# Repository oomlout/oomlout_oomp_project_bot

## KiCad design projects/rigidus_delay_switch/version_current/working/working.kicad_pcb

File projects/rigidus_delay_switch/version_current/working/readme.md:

# OOMP Project  
## delay_switch  by rigidus  
  
oomp key: oomp_projects_flat_rigidus_delay_switch  
(snippet of original readme)  
  
- delay_switch  
  
  full source readme at [readme_src.md](readme_src.md)  
  
source repo at: [https://github.com/rigidus/delay_switch](https://github.com/rigidus/delay_switch)  
## Board  

## Schematic  

[schematic pdf](working_schematic.pdf)  
## Images

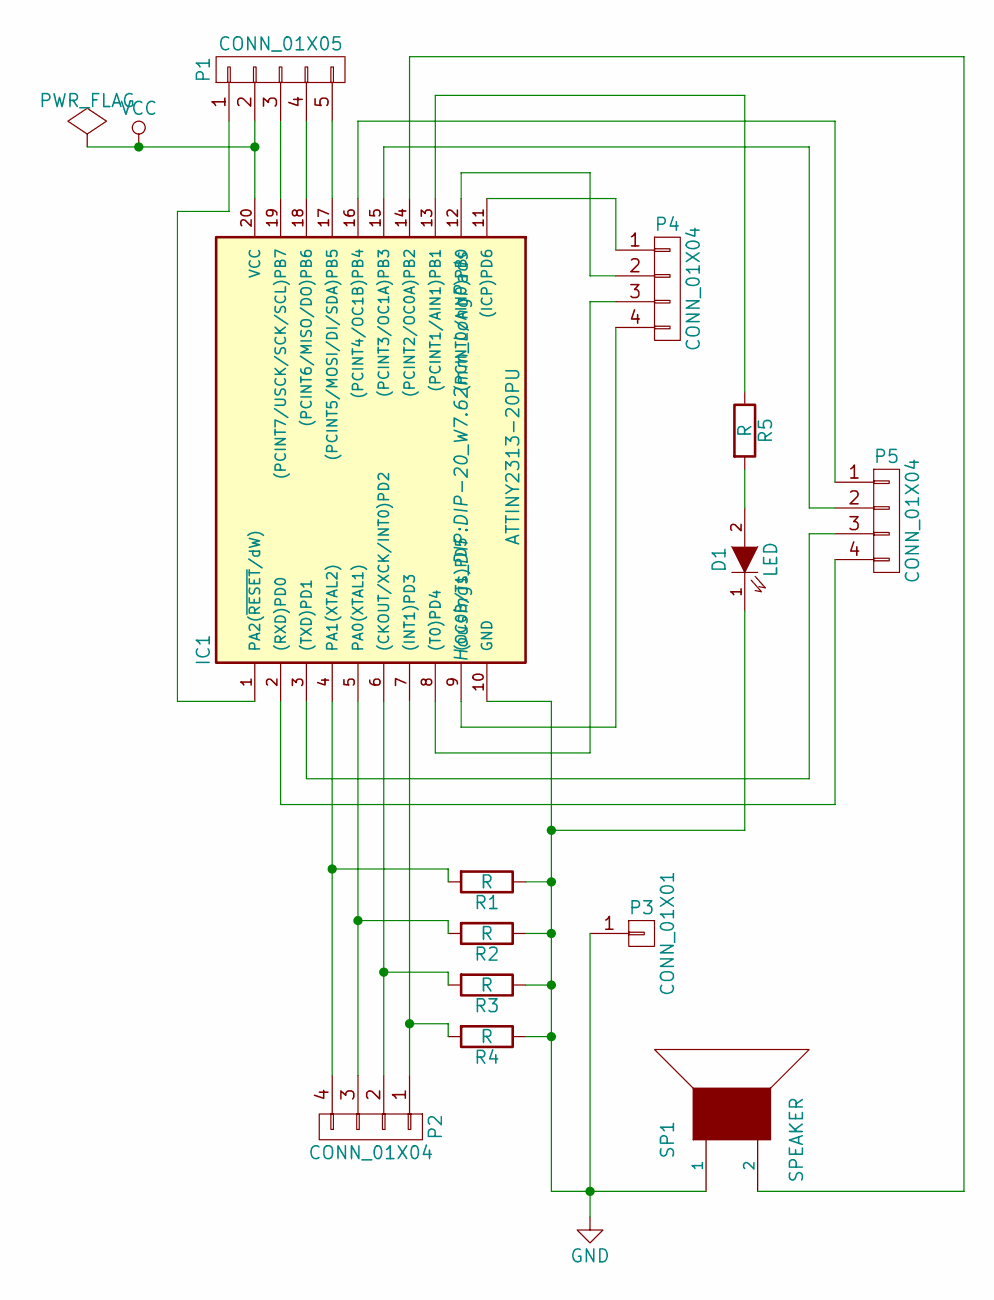
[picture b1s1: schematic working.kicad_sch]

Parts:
D1: LED; LED-3MM
IC1: ATTINY2313-20PU; DIP-20_W7.62mm_LongPads
P1: CONN_01X05; Pin_Header_Straight_1x05
P2, P4, P5: CONN_01X04; Pin_Header_Straight_1x04
P3: CONN_01X01; Pin_Header_Angled_1x01
R1, R2, R3, R4, R5: R; R_1206
SP1: SPEAKER; WireConnection_0.80mmDrill

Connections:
GND: D1.1 (K), IC1.10 (GND), P3.1, R1.1, R2.1, R3.1, R4.1, SP1.1
unnamed: D1.2 (A), R5.2
unnamed: IC1.1 (PA2(~RESET/dW)), P1.1
unnamed: IC1.2 ((RXD)PD0), P5.4
unnamed: IC1.3 ((TXD)PD1), P5.3
unnamed: IC1.4 (PA1(XTAL2)), P2.4, R1.2
unnamed: IC1.5 (PA0(XTAL1)), P2.3, R2.2
unnamed: IC1.6 ((CKOUT/XCK/INT0)PD2), P2.2, R3.2
unnamed: IC1.7 ((INT1)PD3), P2.1, R4.2
unnamed: IC1.8 ((T0)PD4), P4.3
unnamed: IC1.9 ((OC0B/T1)PD5), P4.4
unnamed: IC1.11 ((ICP)PD6), P4.1
unnamed: IC1.12 ((PCINT0/AIN0)PB0), P4.2
unnamed: IC1.13 ((PCINT1/AIN1)PB1), R5.1
unnamed: IC1.14 ((PCINT2/OC0A)PB2), SP1.2
unnamed: IC1.15 ((PCINT3/OC1A)PB3), P5.2
unnamed: IC1.16 ((PCINT4/OC1B)PB4), P5.1
unnamed: IC1.17 ((PCINT5/MOSI/DI/SDA)PB5), P1.5
unnamed: IC1.18 ((PCINT6/MISO/DO)PB6), P1.4
unnamed: IC1.19 ((PCINT7/USCK/SCK/SCL)PB7), P1.3
VCC: IC1.20 (VCC), P1.2

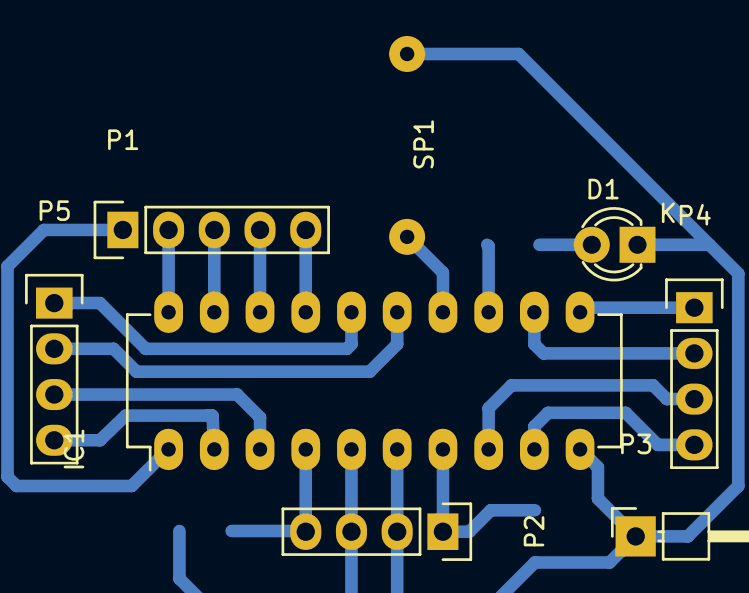
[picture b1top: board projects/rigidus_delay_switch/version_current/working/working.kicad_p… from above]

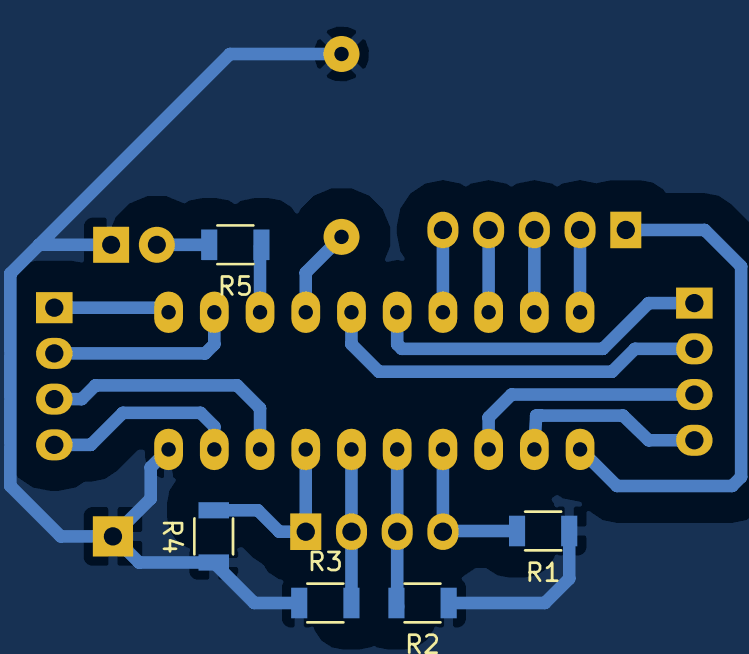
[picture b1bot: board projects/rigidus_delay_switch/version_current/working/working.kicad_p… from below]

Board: 2 copper layers, 13 parts (5 on the bottom side), 21 nets.

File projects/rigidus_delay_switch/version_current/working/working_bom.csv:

"Id";"Designator";"Footprint";"Quantity";"Designation";"Supplier and ref";
1;"D1";"LED-3MM";1;"LED";;;
2;"IC1";"DIP-20_W7.62mm_LongPads";1;"ATTINY2313-20PU";;;
3;"P1";"Pin_Header_Straight_1x05";1;"CONN_01X05";;;
4;"P2,P4,P5";"Pin_Header_Straight_1x04";3;"CONN_01X04";;;
5;"P3";"Pin_Header_Angled_1x01";1;"CONN_01X01";;;
6;"R1,R2,R3,R4,R5";"R_1206";5;"R";;;
7;"SP1";"WireConnection_0.80mmDrill";1;"SPEAKER";;;

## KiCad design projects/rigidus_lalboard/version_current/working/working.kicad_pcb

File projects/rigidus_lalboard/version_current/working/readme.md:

# lalboard by rigidus  
This is a harvested standardized copy of a project from github.  
The original project can be found at:  
https://github.com/rigidus/lalboard  
Please consult that link for additional, details, files, and license information.  
Note: It was auto harvested and if the original repo had more than one board file or anything out of the ordinary the files here are likely not representative.

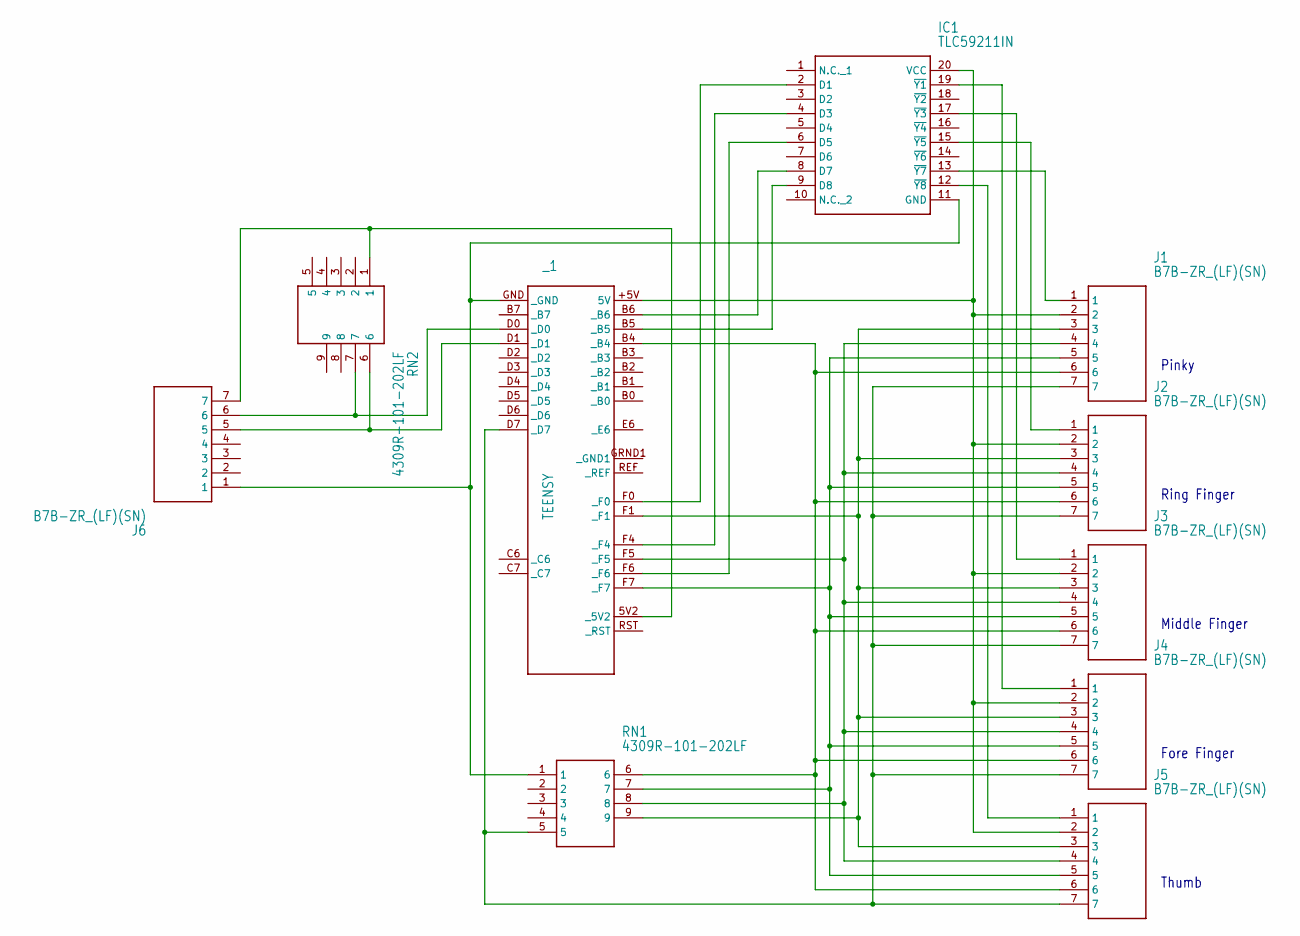
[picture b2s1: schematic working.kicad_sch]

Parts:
IC1: TLC59211IN; DIP794W53P254L2540H508Q20N
J1, J2, J3, J4, J5, J6: B7B-ZR_(LF)(SN); SHDR7W50P0X150_1X7_1200X350X45
RN1, RN2: 4309R-101-202LF; 4309R-101
_1: TEENSY

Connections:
unnamed: IC1.20 (VCC), J1.2, J2.2, J3.2, J4.2, J5.2, _1.+5V (5V)
unnamed: J1.3, J2.3, J3.3, J4.3, J5.3, RN1.9, _1.F1 (_F1)
unnamed: J1.6, J2.6, J3.6, J4.6, J5.6, RN1.6, _1.B4 (_B4)
unnamed: J1.4, J2.4, J3.4, J4.4, J5.4, RN1.8, _1.F5 (_F5)
unnamed: J1.5, J2.5, J3.5, J4.5, J5.5, RN1.7, _1.F7 (_F7)
unnamed: IC1.11 (GND), J6.1, RN1.1, _1.GND (_GND)
unnamed: J1.7, J2.7, J3.7, J4.7, J5.7, RN1.5, _1.D7 (_D7)
unnamed: IC1.8 (D7), _1.B6 (_B6)
unnamed: IC1.9 (D8), _1.B5 (_B5)
unnamed: IC1.6 (D5), _1.F6 (_F6)
unnamed: IC1.4 (D3), _1.F4 (_F4)
unnamed: IC1.2 (D1), _1.F0 (_F0)
unnamed: IC1.15 (~Y5), J2.1
unnamed: J6.5, RN2.6, _1.D1 (_D1)
unnamed: J6.7, RN2.1, _1.5V2 (_5V2)
unnamed: J6.6, RN2.7, _1.D0 (_D0)
unnamed: IC1.17 (~Y3), J3.1
unnamed: IC1.19 (~Y1), J4.1
unnamed: IC1.12 (~Y8), J5.1
unnamed: IC1.13 (~Y7), J1.1

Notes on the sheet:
Thumb
Middle Finger
Fore Finger
Ring Finger
Pinky

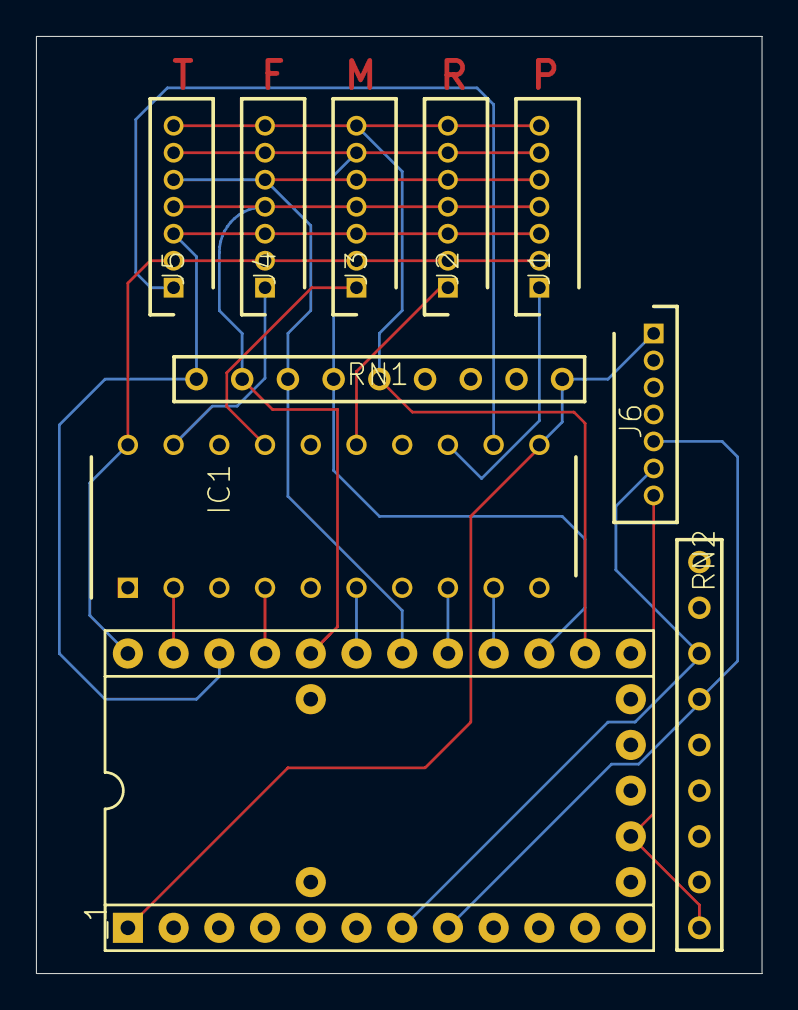
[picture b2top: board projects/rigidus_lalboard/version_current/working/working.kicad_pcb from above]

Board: 2 copper layers, 40.3 x 52.1 mm, 10 parts (0 on the bottom side), 20 nets.

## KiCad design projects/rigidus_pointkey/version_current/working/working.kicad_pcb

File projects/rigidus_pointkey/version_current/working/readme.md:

# pointkey by rigidus  
This is a harvested standardized copy of a project from github.  
The original project can be found at:  
https://github.com/rigidus/pointkey  
Please consult that link for additional, details, files, and license information.  
Note: It was auto harvested and if the original repo had more than one board file or anything out of the ordinary the files here are likely not representative.

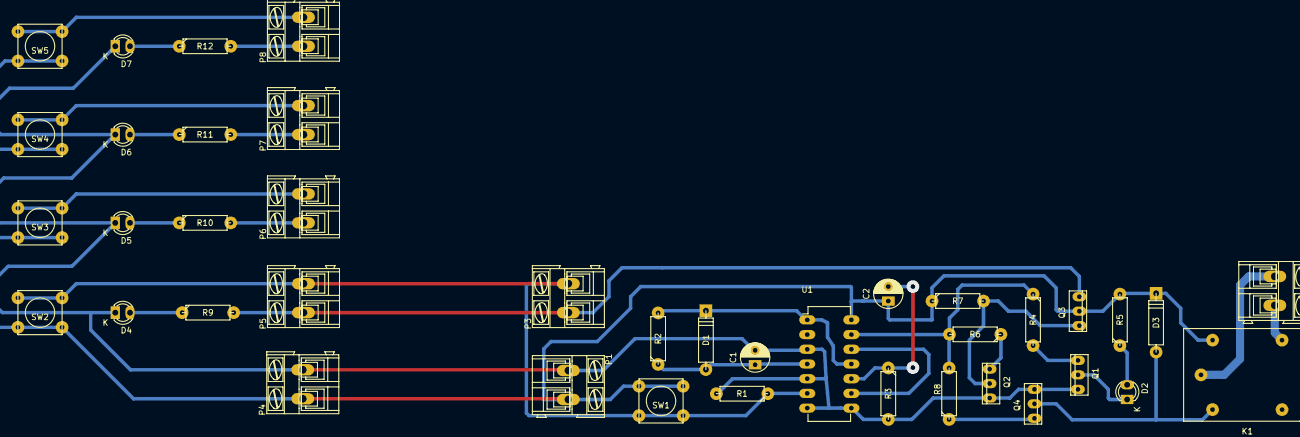
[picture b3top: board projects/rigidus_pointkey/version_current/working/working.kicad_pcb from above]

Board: 2 copper layers, 40 parts (0 on the bottom side), 28 nets.

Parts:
C1: 1u; C_Radial_D5_L6_P2.5
C2: 20u; C_Radial_D5_L6_P2.5
D1, D3: D; D4
D2, D4, D5, D6, D7: LED; LED-3MM
K1: RELAY_1RT; RELAY_812H_1C_C
P1, P2, P3, P4, P5, P6, P7, P8: CONN_01X02; AK300-2
Q1, Q2, Q3, Q4: КТ315; кт-13
R1, R3: 22k; R3-5
R2: 510k; R3-5
R4, R5, R6: 100; R3-5
R7: 1K; R3-5
R8: 1k; R3-5
R9, R10, R11, R12: R; R3-5
SW1, SW2, SW3, SW4, SW5: SW_PUSH; SW_PUSH_SMALL
U1: 4013; DIP-14_W7.62mm

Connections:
GND: C1.2, D4.1, D5.1, D6.1, D7.1, P1.1, P4.2, Q1.3, Q2.3, Q4.3, R1.2, R3.2, U1.3, U1.5, U1.7, U1.8
IND_1: P3.1, P5.1, Q3.3, R9.2
IND_2: P6.1, R10.2
IND_3: P7.1, R11.2
IND_4: P8.1, R12.2
unnamed: C1.1, D1.2, R2.1, U1.4
unnamed: C2.2, R3.1, U1.10
unnamed: D1.1, R2.2, U1.1, U1.11
unnamed: D2.1, Q1.1
unnamed: D2.2, R5.1
unnamed: D3.2, K1.2, Q4.1
unnamed: D4.2, R9.1
unnamed: D5.2, R10.1
unnamed: D6.2, R11.1
unnamed: D7.2, R12.1
unnamed: K1.3, P2.1
unnamed: K1.5, P2.2
unnamed: Q1.2, R4.2
unnamed: Q2.1, Q3.2, R7.2
unnamed: Q2.2, R6.1
unnamed: Q4.2, R8.1
unnamed: R4.1, R6.2, R8.2, U1.13
unnamed: U1.9, U1.12
SWI_1: P3.2, P5.2, R1.1, SW1.1, SW2.2, U1.6
SWI_2: P6.2, SW3.2
SWI_3: P7.2, SW4.2
SWI_4: P8.2, SW5.2
VCC: C2.1, D3.1, K1.1, P1.2, P4.1, Q3.1, R5.2, R7.1, SW1.2, SW2.1, SW3.1, SW4.1, SW5.1, U1.14

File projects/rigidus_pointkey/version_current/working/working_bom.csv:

"Id";"Designator";"Footprint";"Quantity";"Designation";"Supplier and ref";
1;"SW2,SW1,SW3,SW4,SW5";"SW_PUSH_SMALL";5;"SW_PUSH";;;
2;"R3,R1";"R3-5";2;"22k";;;
3;"C1";"C_Radial_D5_L6_P2.5";1;"1u";;;
4;"C2";"C_Radial_D5_L6_P2.5";1;"20u";;;
5;"D1,D3";"D4";2;"D";;;
6;"D2,D4,D5,D6,D7";"LED-3MM";5;"LED";;;
7;"K1";"RELAY_812H_1C_C";1;"RELAY_1RT";;;
8;"Q1,Q2,Q3,Q4";"кт-13";4;"КТ315";;;
9;"R2";"R3-5";1;"510k";;;
10;"R4,R5,R6";"R3-5";3;"100";;;
11;"R7";"R3-5";1;"1K";;;
12;"R8";"R3-5";1;"1k";;;
13;"U1";"DIP-14_W7.62mm";1;"4013";;;
14;"R9,R10,R11,R12";"R3-5";4;"R";;;

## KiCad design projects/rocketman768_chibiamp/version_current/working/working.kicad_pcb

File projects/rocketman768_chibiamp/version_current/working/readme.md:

# ChibiAmp by rocketman768  
This is a harvested standardized copy of a project from github.  
The original project can be found at:  
https://github.com/rocketman768/ChibiAmp  
Please consult that link for additional, details, files, and license information.  
Note: It was auto harvested and if the original repo had more than one board file or anything out of the ordinary the files here are likely not representative.

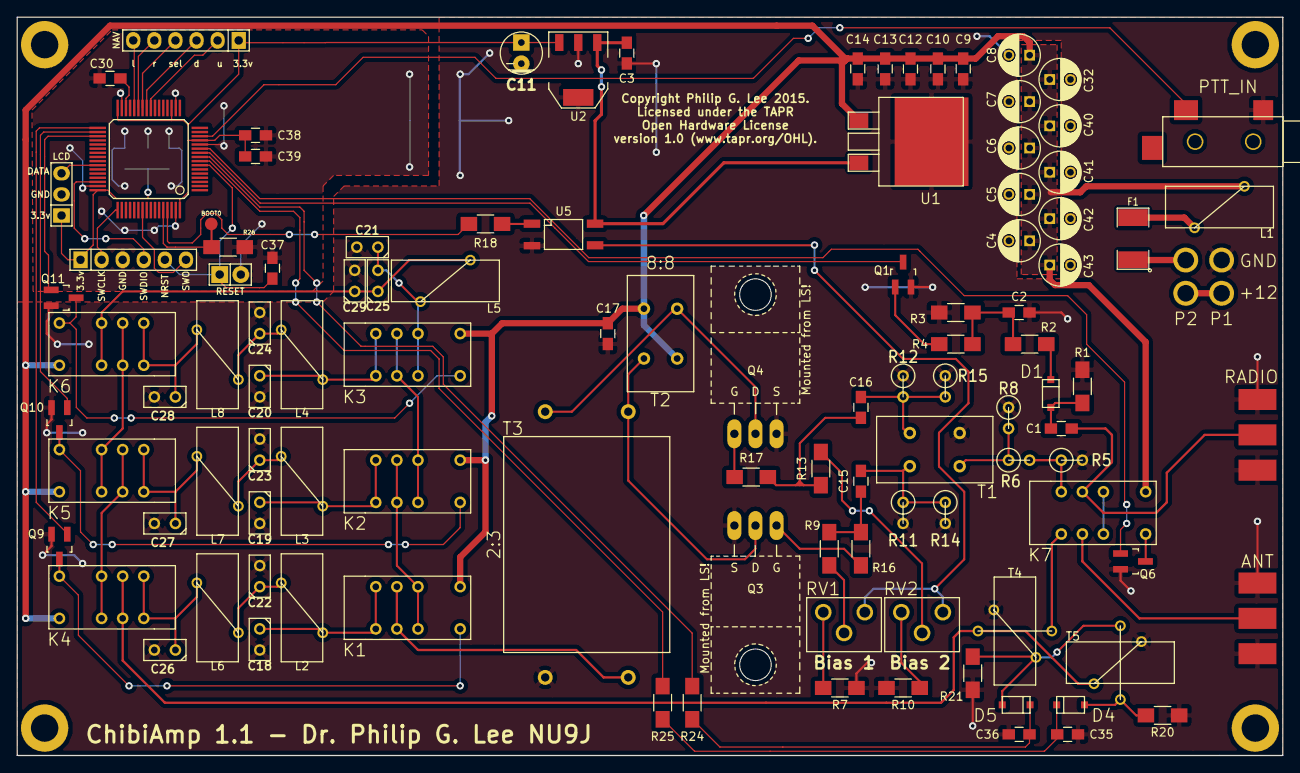
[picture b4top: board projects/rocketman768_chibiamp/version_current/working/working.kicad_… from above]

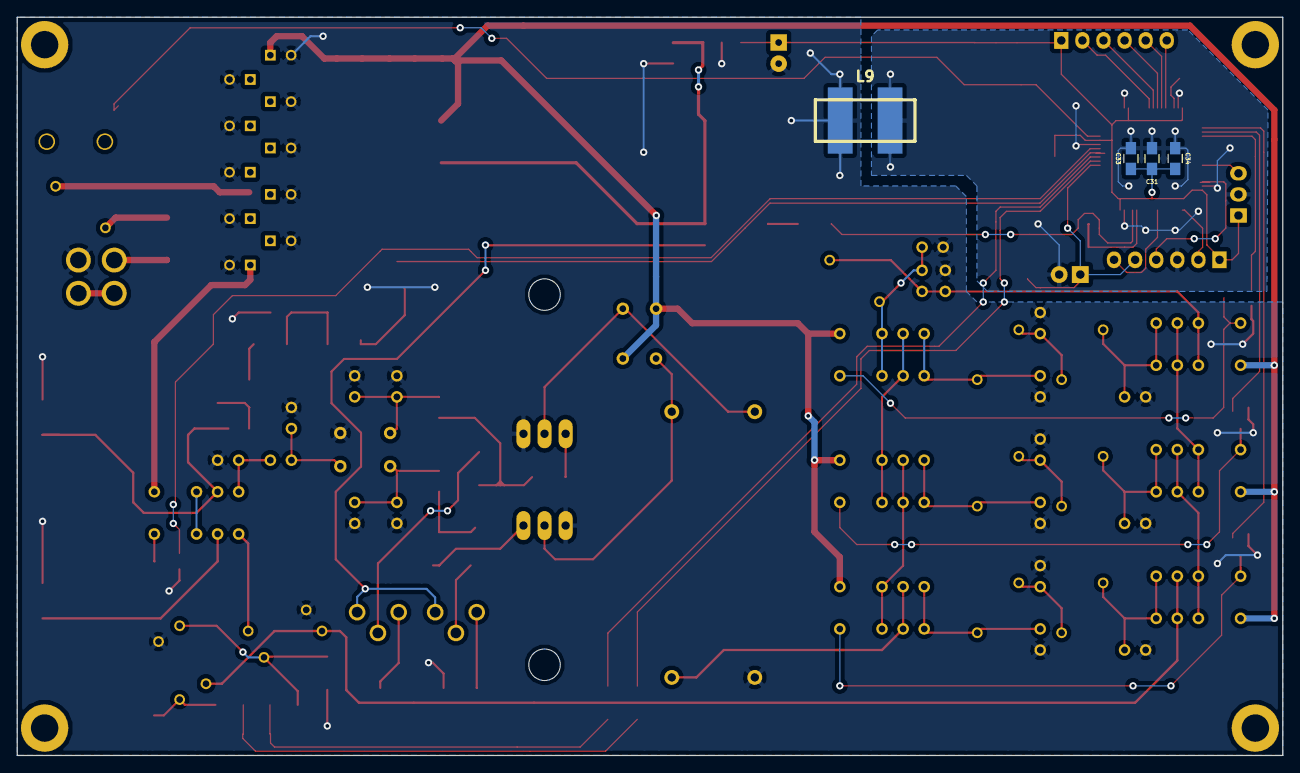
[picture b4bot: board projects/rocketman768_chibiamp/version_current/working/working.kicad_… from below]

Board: 2 copper layers, 152.4 x 88.9 mm, 118 parts (4 on the bottom side), 78 nets.

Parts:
C1, C2, C3, C9, C10, C12, C13, C14, C33, C34, C37: .1u; C_0805_HandSoldering
C4, C5, C6, C7, C8, C32, C40, C41, C42, C43: 10u; C_Radial_D5_L11_P2.5
C11: 10u; Capacitor5x11RM2.5
C15, C16, C17, C35, C36: 0.1u; C_0805_HandSoldering
C18, C25, C26: 150p; C1
C19, C27: 330p; C1
C20, C28: 560p; C1
C21, C29: 1800p; C1
C22: 270p; C1
C23: 680p; C1
C24: 1000p; C1
C30, C31: 4.7u; C_0805_HandSoldering
C38: .01u; C_0805_HandSoldering
C39: 1u; C_0805_HandSoldering
D1, D4, D5: SD101; SOD-123
F1: PTS18128V200; SMD-1812_l
K1: BAND3_IN; EC2-12NU
K2: BAND2_IN; EC2-12NU
K3: BAND1_IN; EC2-12NU
K4: BAND3_OUT; EC2-12NU
K5: BAND2_OUT; EC2-12NU
K6: BAND1_OUT; EC2-12NU
K7: ANT_RLY; EC2-12NU
L1: 500u; TOROID-50
L2, L6: T50-6 8T; TOROID-50
L3, L7: T50-6 9T; TOROID-50
L4, L8: T50-2 12T; TOROID-50
L5: T50-2 17T; TOROID-50
L9: BEAD; WE-SUCKW
Mounting Hole: VAL**; MountingHole4-40
Mounting Hole#2, Mounting Hole#3, Mounting Hole#4: VAL**; MountingHole4-40
P1: PWR; PWR2-16AWG
P2: PWR_SW; PWR2-16AWG
P3: SWD; Pin_Header_Straight_1x06
P4: ANT; SMA-EDGE-0.375in
P5: RADIO; SMA-EDGE-0.375in
P6: PTT_IN; 3.5MM_SWITCHCRAFT-35RASMT2AHNTRX
P7: TP; Measurement_Point_Round-SMD-Pad_Small
P8: NAV_BUTTON; Pin_Header_Straight_1x06
Q1: MMBT6427; SOT-23-EBC_HandSoldering
Q3, Q4: IRF510; TO-220_FET-GDS_Horizontal_MountedFromLS_LargePads
Q6, Q9, Q10, Q11: MMBF170; SOT-23-DGS_HandSoldering
R1, R4, R9, R13, R26: 10k; R_1206_HandSoldering
R2: 680; R_1206_HandSoldering
R3: 6.8k; R_1206_HandSoldering
R5, R8: 300; R1
R6: 18; R1
R7, R10: 5k; R_1206_HandSoldering
R11, R12, R14, R15: 51; R1
R16, R17: 10; R_1206_HandSoldering
R18: 150; R_1206_HandSoldering
R20, R21: 51; R_1206_HandSoldering
R24, R25: 50k; R_1206_HandSoldering
RV1, RV2: 5k; Potentiometer_Trimmer_Piher_PT10_H01
SW1: SW_PUSH; Pin_Header_Straight_1x02
T1, T2: 8:8; BN2-202
T3: 2:3; BN2-3312
T4: 12:1; TOROID2-50-singleturn
T5: 1:12; TOROID2-50-singleturn
U1: LM7805; DPAK-3_VIVOGND
U2: LM3940; SOT-223
U3: LCD-2x16; Pin_Header_Straight_1x03
U4: STM32F401xB/C-LQFP; LQFP64
U5: LTV-356T; Optocoupler_SMD_HandSoldering_KPC357_LTV35x_PC357_SingleCha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

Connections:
+3.3V: C11.1, C31.1, C33.1, C34.1, C38.1, C39.1, P3.1, P8.1, U2.VO, U3.1, U4.13, U4.19, U4.32, U4.48, U4.64
+5V: C3.1, U1.VO, U2.VI, U5.4
+12V: C4.1, C5.1, C6.1, C7.1, C8.1, C9.1, C10.1, C12.1, C13.1, C14.1, C17.2, C32.1, C40.1, C41.1, C42.1, C43.1, K1.1, K2.1, K3.1, K4.1, K5.1, K6.1, K7.1, L1.2, T2.1, T2.4, U1.VI
/Amplifier/amp_in: K7.5, R5.1, R6.2
/Amplifier/amp_on: R18.2, U4.61
/Amplifier/amp_out: K1.4, K1.9, T3.3
/Amplifier/vb1: C15.1, R9.1, R16.2
/Amplifier/vb2: C16.1, R13.1, R17.2
/Band Filters/band1_sel: K3.12, K6.12, Q11.D
/Band Filters/band2_sel: K2.12, K5.12, Q10.D
/Band Filters/band3_sel: K1.12, K4.12, Q9.D
/Band Filters/bandfilter_1sel: Q11.G, U4.35
/Band Filters/bandfilter_2sel: Q10.G, U4.34
/Band Filters/bandfilter_3sel: Q9.G, U4.33
/Band Filters/bandfilter_out: K4.4, K4.9, T4.1, T5.4
/Microcontroller/NRST: C37.1, P3.5, SW1.1, U4.7
/Microcontroller/SWCLK: P3.2, U4.49
/Microcontroller/SWDIO: P3.4, U4.46
/Microcontroller/SWO: P3.6, U4.55
/Microcontroller/mcu_ptt: P6.2, U4.14
/Microcontroller/mcu_rfdet: Q1.c, U4.10
/Microcontroller/mcu_swr_fwd: C36.1, D5.2, R25.1
/Microcontroller/mcu_swr_ref: C35.1, D4.2, R24.2
/Microcontroller/nav_down: P8.3, U4.25
/Microcontroller/nav_left: P8.6, U4.28
/Microcontroller/nav_right: P8.5, U4.27
/Microcontroller/nav_select: P8.4, U4.26
/Microcontroller/nav_up: P8.2, U4.24
/RF In/Out/ant_sw_rly: Q6.G, U4.11
/RF In/Out/from_final: K7.8, T4.2
/RF In/Out/raw_input: C1.2, K7.4, P5.1
DGND: C30.1, C31.2, C33.2, C34.2, C37.2, C38.2, C39.2, L9.2, P3.3, R26.1, SW1.2, U3.2, U4.12, U4.18, U4.31, U4.47, U4.63
GND: C2.1, C3.2, C4.2, C5.2, C6.2, C7.2, C8.2, C9.2, C10.2, C11.2, C12.2, C13.2, C14.2, C17.1, C18.2, C19.2, C20.2, C21.2, C22.2, C23.2, C24.2, C26.2, C27.2, C28.2, C29.2, C32.2, C35.2, C36.2, C40.2, C41.2, C42.2, C43.2, L9.1, P1.1, P4.2, P5.2, P6.1, Q1.e, Q3.S, Q4.S, Q6.S, Q9.S, Q10.S, Q11.S, R1.2, R3.1, R5.2, R7.2, R8.1, R10.2, R11.2, R12.1, R14.2, R15.1, R20.2, R21.2, T1.1, T3.4, T4.3, T5.3, U1.GND, U2.GND, U5.2
unnamed: C1.1, D1.1, R1.1
unnamed: C2.2, R2.1, R3.2, R4.2
unnamed: C15.2, R11.1, R14.1, T1.4
unnamed: C16.2, R12.2, R15.2, T1.2
unnamed: C18.1, K1.5, K1.8, L2.1
unnamed: C19.1, K2.5, K2.8, L3.1
unnamed: C20.1, K3.5, K3.8, L4.1
unnamed: C21.1, C25.2, K3.3, K3.10, L5.1
unnamed: C22.1, L2.2, L6.1
unnamed: C23.1, L3.2, L7.1
unnamed: C24.1, L4.2, L8.1
unnamed: C25.1, C29.1, K6.3, K6.10, L5.2
unnamed: C26.1, K4.5, K4.8, L6.2
unnamed: C27.1, K5.5, K5.8, L7.2
unnamed: C28.1, K6.5, K6.8, L8.2
unnamed: C30.2, U4.30
unnamed: D1.2, R2.2
unnamed: D4.1, R20.1, T5.2
unnamed: D5.1, R21.1, T4.4, T5.1
unnamed: F1.1, P2.2
unnamed: F1.2, L1.1
unnamed: K1.3, K1.10, K2.4, K2.9
unnamed: K2.3, K2.10, K3.4, K3.9
unnamed: K4.3, K4.10, K5.4, K5.9
unnamed: K5.3, K5.10, K6.4, K6.9
unnamed: K7.9, P4.1
unnamed: K7.3, K7.10
unnamed: K7.12, Q6.D
unnamed: P1.2, P2.1
unnamed: P7.1, R26.2, U4.60
unnamed: Q1.b, R4.1
unnamed: Q3.D, T2.3, T3.1
unnamed: Q3.G, R16.1
unnamed: Q4.D, T2.2, T3.2
unnamed: Q4.G, R17.1
unnamed: R6.1, R8.2, T1.3
unnamed: R7.1, RV1.3
unnamed: R9.2, RV1.2
unnamed: R10.1, RV2.3
unnamed: R13.2, RV2.2
unnamed: R18.1, U5.1
unnamed: R24.1, U4.8
unnamed: R25.2, U4.9
unnamed: RV1.1, RV2.1, U5.3
unnamed: U3.3, U4.42

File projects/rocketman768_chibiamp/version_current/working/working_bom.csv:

"Id";"Designator";"Footprint";"Quantity";"Designation";"Supplier and ref";
1;"U2";"SOT-223";1;"LM3940";;;
2;"RV2,RV1";"Potentiometer_Trimmer_Piher_PT10_H01";2;"5k";;;
3;"Q3,Q4";"TO-220_FET-GDS_Horizontal_MountedFromLS_LargePads";2;"IRF510";;;
4;"P1";"PWR2-16AWG";1;"PWR";;;
5;"U5";"Optocoupler_SMD_HandSoldering_KPC357_LTV35x_PC357_SingleChannel";1;"LTV-356T";;;
6;"L9";"WE-SUCKW";1;"BEAD";;;
7;"U4";"LQFP64";1;"STM32F401xB/C-LQFP";;;
8;"L1";"TOROID-50";1;"500u";;;
9;"K7";"EC2-12NU";1;"ANT_RLY";;;
10;"K5";"EC2-12NU";1;"BAND2_OUT";;;
11;"K4";"EC2-12NU";1;"BAND3_OUT";;;
12;"K1";"EC2-12NU";1;"BAND3_IN";;;
13;"K2";"EC2-12NU";1;"BAND2_IN";;;
14;"K3";"EC2-12NU";1;"BAND1_IN";;;
15;"K6";"EC2-12NU";1;"BAND1_OUT";;;
16;"P4";"SMA-EDGE-0.375in";1;"ANT";;;
17;"P5";"SMA-EDGE-0.375in";1;"RADIO";;;
18;"D1,D4,D5";"SOD-123";3;"SD101";;;
19;"T4";"TOROID2-50-singleturn";1;"12:1";;;
20;"T5";"TOROID2-50-singleturn";1;"1:12";;;
21;"L4,L8";"TOROID-50";2;"T50-2 12T";;;
22;"L3,L7";"TOROID-50";2;"T50-6 9T";;;
23;"L5";"TOROID-50";1;"T50-2 17T";;;
24;"L6,L2";"TOROID-50";2;"T50-6 8T";;;
25;"C1,C2,C3,C9,C10,C12,C13,C14,C33,C34,C37";"C_0805_HandSoldering";11;".1u";;;
26;"C11";"Capacitor5x11RM2.5";1;"10u";;;
27;"C15,C16,C17,C35,C36";"C_0805_HandSoldering";5;"0.1u";;;
28;"C18,C25,C26";"C1";3;"150p";;;
29;"C19,C27";"C1";2;"330p";;;
30;"C20,C28";"C1";2;"560p";;;
31;"C21,C29";"C1";2;"1800p";;;
32;"C22";"C1";1;"270p";;;
33;"C23";"C1";1;"680p";;;
34;"C24";"C1";1;"1000p";;;
35;"F1";"SMD-1812_l";1;"PTS18128V200";;;
36;"P2";"PWR2-16AWG";1;"PWR_SW";;;
37;"P6";"3.5MM_SWITCHCRAFT-35RASMT2AHNTRX";1;"PTT_IN";;;
38;"R1,R4,R9,R13,R26";"R_1206_HandSoldering";5;"10k";;;
39;"R2";"R_1206_HandSoldering";1;"680";;;
40;"R3";"R_1206_HandSoldering";1;"6.8k";;;
41;"R5,R8";"R1";2;"300";;;
42;"R6";"R1";1;"18";;;
43;"R7,R10";"R_1206_HandSoldering";2;"5k";;;
44;"R11,R12,R14,R15";"R1";4;"51";;;
45;"R16,R17";"R_1206_HandSoldering";2;"10";;;
46;"R20,R21";"R_1206_HandSoldering";2;"51";;;
47;"T1,T2";"BN2-202";2;"8:8";;;
48;"T3";"BN2-3312";1;"2:3";;;
49;"U3";"Pin_Header_Straight_1x03";1;"LCD-2x16";;;
50;"U1";"DPAK-3_VIVOGND";1;"LM7805";;;
51;"C38";"C_0805_HandSoldering";1;".01u";;;
52;"C30,C31";"C_0805_HandSoldering";2;"4.7u";;;
53;"P3";"Pin_Header_Straight_1x06";1;"SWD";;;
54;"R24,R25";"R_1206_HandSoldering";2;"50k";;;
55;"SW1";"Pin_Header_Straight_1x02";1;"SW_PUSH";;;
56;"P8";"Pin_Header_Straight_1x06";1;"NAV_BUTTON";;;
57;"P7";"Measurement_Point_Round-SMD-Pad_Small";1;"TP";;;
58;"Mounting Hole,Mounting Hole,Mounting Hole,Mounting Hole";"MountingHole4-40";4;"VAL**";;;
59;"Q1";"SOT-23-EBC_HandSoldering";1;"MMBT6427";;;
60;"Q6,Q9,Q10,Q11";"SOT-23-DGS_HandSoldering";4;"MMBF170";;;
61;"R18";"R_1206_HandSoldering";1;"150";;;
62;"C32,C40,C41,C42,C43,C4,C5,C6,C7,C8";"C_Radial_D5_L11_P2.5";10;"10u";;;
63;"C39";"C_0805_HandSoldering";1;"1u";;;

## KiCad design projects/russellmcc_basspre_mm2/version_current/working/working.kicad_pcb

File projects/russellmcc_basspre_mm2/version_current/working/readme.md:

# basspre-mm2 by russellmcc  
This is a harvested standardized copy of a project from github.  
The original project can be found at:  
https://github.com/russellmcc/basspre-mm2  
Please consult that link for additional, details, files, and license information.  
Note: It was auto harvested and if the original repo had more than one board file or anything out of the ordinary the files here are likely not representative.

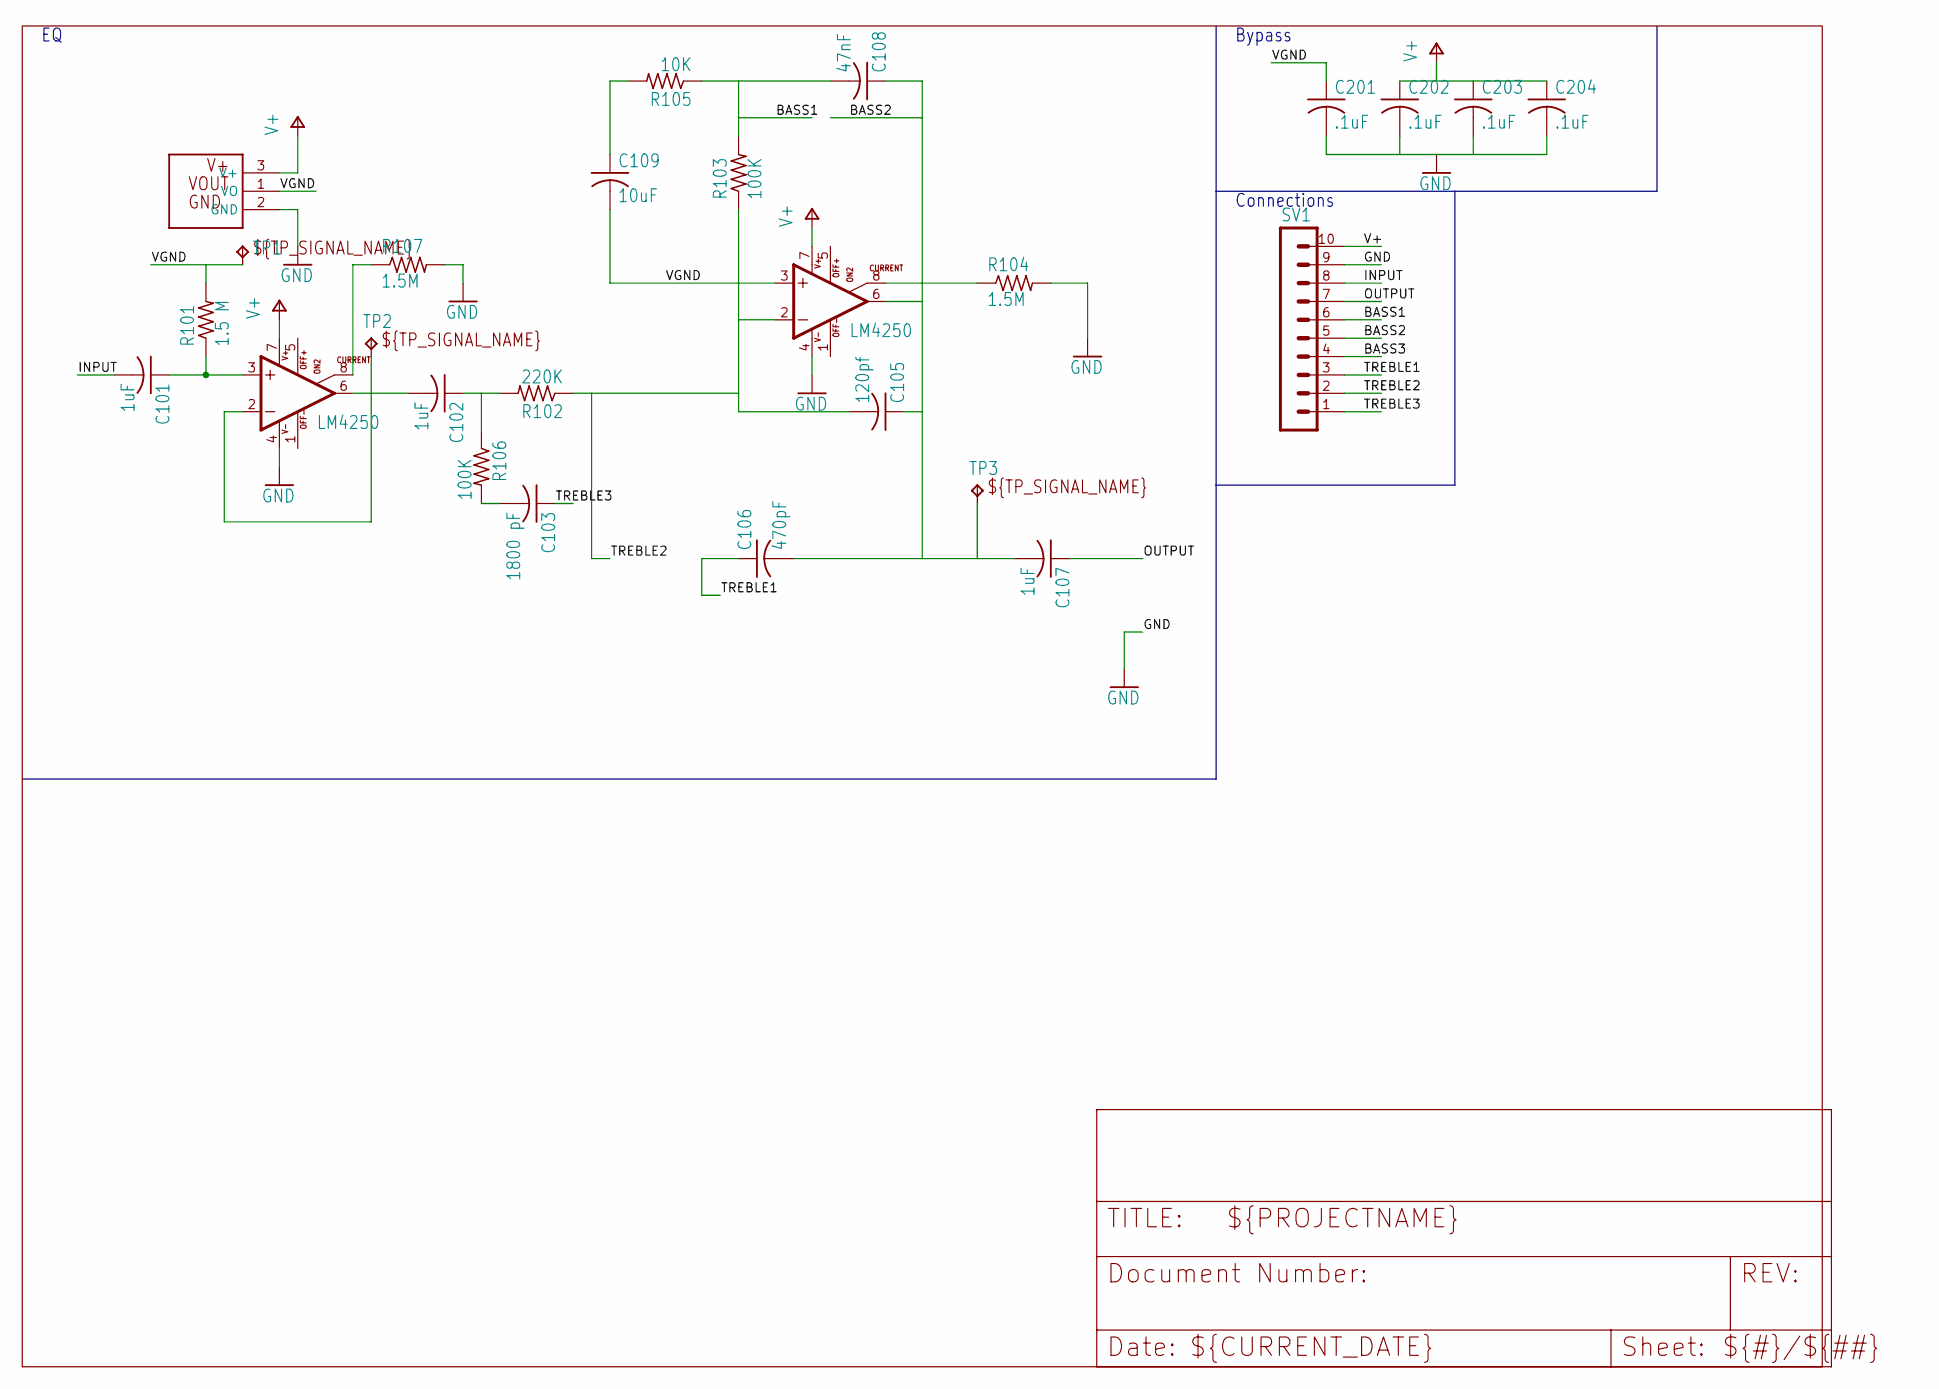
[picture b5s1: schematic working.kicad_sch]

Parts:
C101, C102, C107: 1uF; C0805
C103: 1800 pF; C0603
C105: 120pf; C0603
C106: 470pF; C0603
C108: 47nF; C0603
C109: 10uF; C0805
C201, C202, C203, C204: .1uF; C0603
R101: 1.5 M; R0603
R102: 220K; R0603
R103, R106: 100K; R0603
R104, R107: 1.5M; R0603
R105: 10K; R0603
SV1: MA10-1
TP1, TP2, TP3: TPPAD1-13; P1-13
U1, U103: LM4250; SOIC8
U101: TLE2426IDR; SOIC8

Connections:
BASS1: C108.2, R103.2, R105.1, SV1.6
BASS2: C105.1, C106.2, C107.2, C108.1, SV1.5, TP3.TP, U103.6 (OUT)
BASS3: SV1.4
C1: C101.1, R101.1, U1.3 (+IN)
GND: C201.2, C202.2, C203.2, C204.2, R104.2, R107.2, SV1.9, U1.4 (V-), U101.2 (GND), U103.4 (V-)
INPUT: C101.2, SV1.8
unnamed: C102.1, R102.2, R106.1
unnamed: R104.1, U103.8 (CURRENT)
unnamed: C102.2, TP2.TP, U1.2 (-IN), U1.6 (OUT)
unnamed: C109.1, R105.2
unnamed: C103.2, R106.2
OUTPUT: C107.1, SV1.7
R107: R107.1, U1.8 (CURRENT)
TREBLE1: C106.1, SV1.3
TREBLE2: C105.2, R102.1, R103.1, SV1.2, U103.2 (-IN)
TREBLE3: C103.1, SV1.1
V+: C202.1, C203.1, C204.1, SV1.10, U1.7 (V+), U101.3 (V+), U103.7 (V+)
VGND: C109.2, C201.1, R101.2, TP1.TP, U101.1 (VO), U103.3 (+IN)

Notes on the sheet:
Bypass
Connections

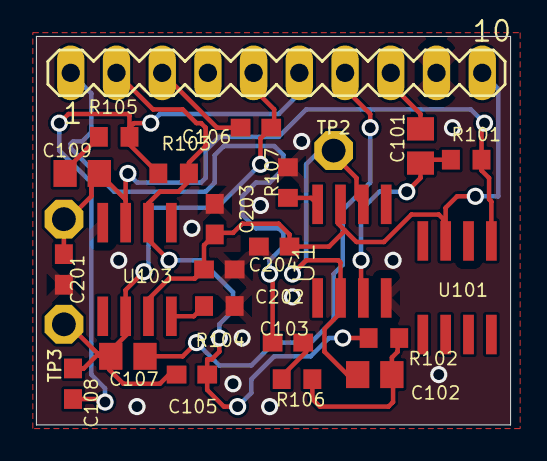
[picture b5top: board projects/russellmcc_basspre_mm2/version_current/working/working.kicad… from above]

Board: 2 copper layers, 26.3 x 21.6 mm, 27 parts (1 on the bottom side), 17 nets.

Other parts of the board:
U$1: OSHW-LOGO-L

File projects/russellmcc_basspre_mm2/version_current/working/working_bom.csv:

"Id";"Designator";"Footprint";"Quantity";"Designation";"Supplier and ref";
1;"C108";"C0603";1;"47nF";;;
2;"C102,C107,C101";"C0805";3;"1uF";;;
3;"TP3,TP1,TP2";"P1-13";3;"TPPAD1-13";;;
4;"C106";"C0603";1;"470pF";;;
5;"C202,C204,C203,C201";"C0603";4;".1uF";;;
6;"C109";"C0805";1;"10uF";;;
7;"R105";"R0603";1;"10K";;;
8;"R102";"R0603";1;"220K";;;
9;"R101";"R0603";1;"1.5 M";;;
10;"R103,R106";"R0603";2;"100K";;;
11;"R107,R104";"R0603";2;"1.5M";;;
12;"C103";"C0603";1;"1800 pF";;;
13;"U1,U103";"SOIC8";2;"LM4250";;;
14;"U101";"SOIC8";1;"TLE2426IDR";;;
15;"C105";"C0603";1;"120pf";;;
16;"SV1";"MA10-1";1;"";;;
17;"U$1";"OSHW-LOGO-L";1;"";;;

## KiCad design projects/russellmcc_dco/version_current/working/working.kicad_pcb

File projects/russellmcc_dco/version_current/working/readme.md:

# dco by russellmcc  
This is a harvested standardized copy of a project from github.  
The original project can be found at:  
https://github.com/russellmcc/dco  
Please consult that link for additional, details, files, and license information.  
Note: It was auto harvested and if the original repo had more than one board file or anything out of the ordinary the files here are likely not representative.

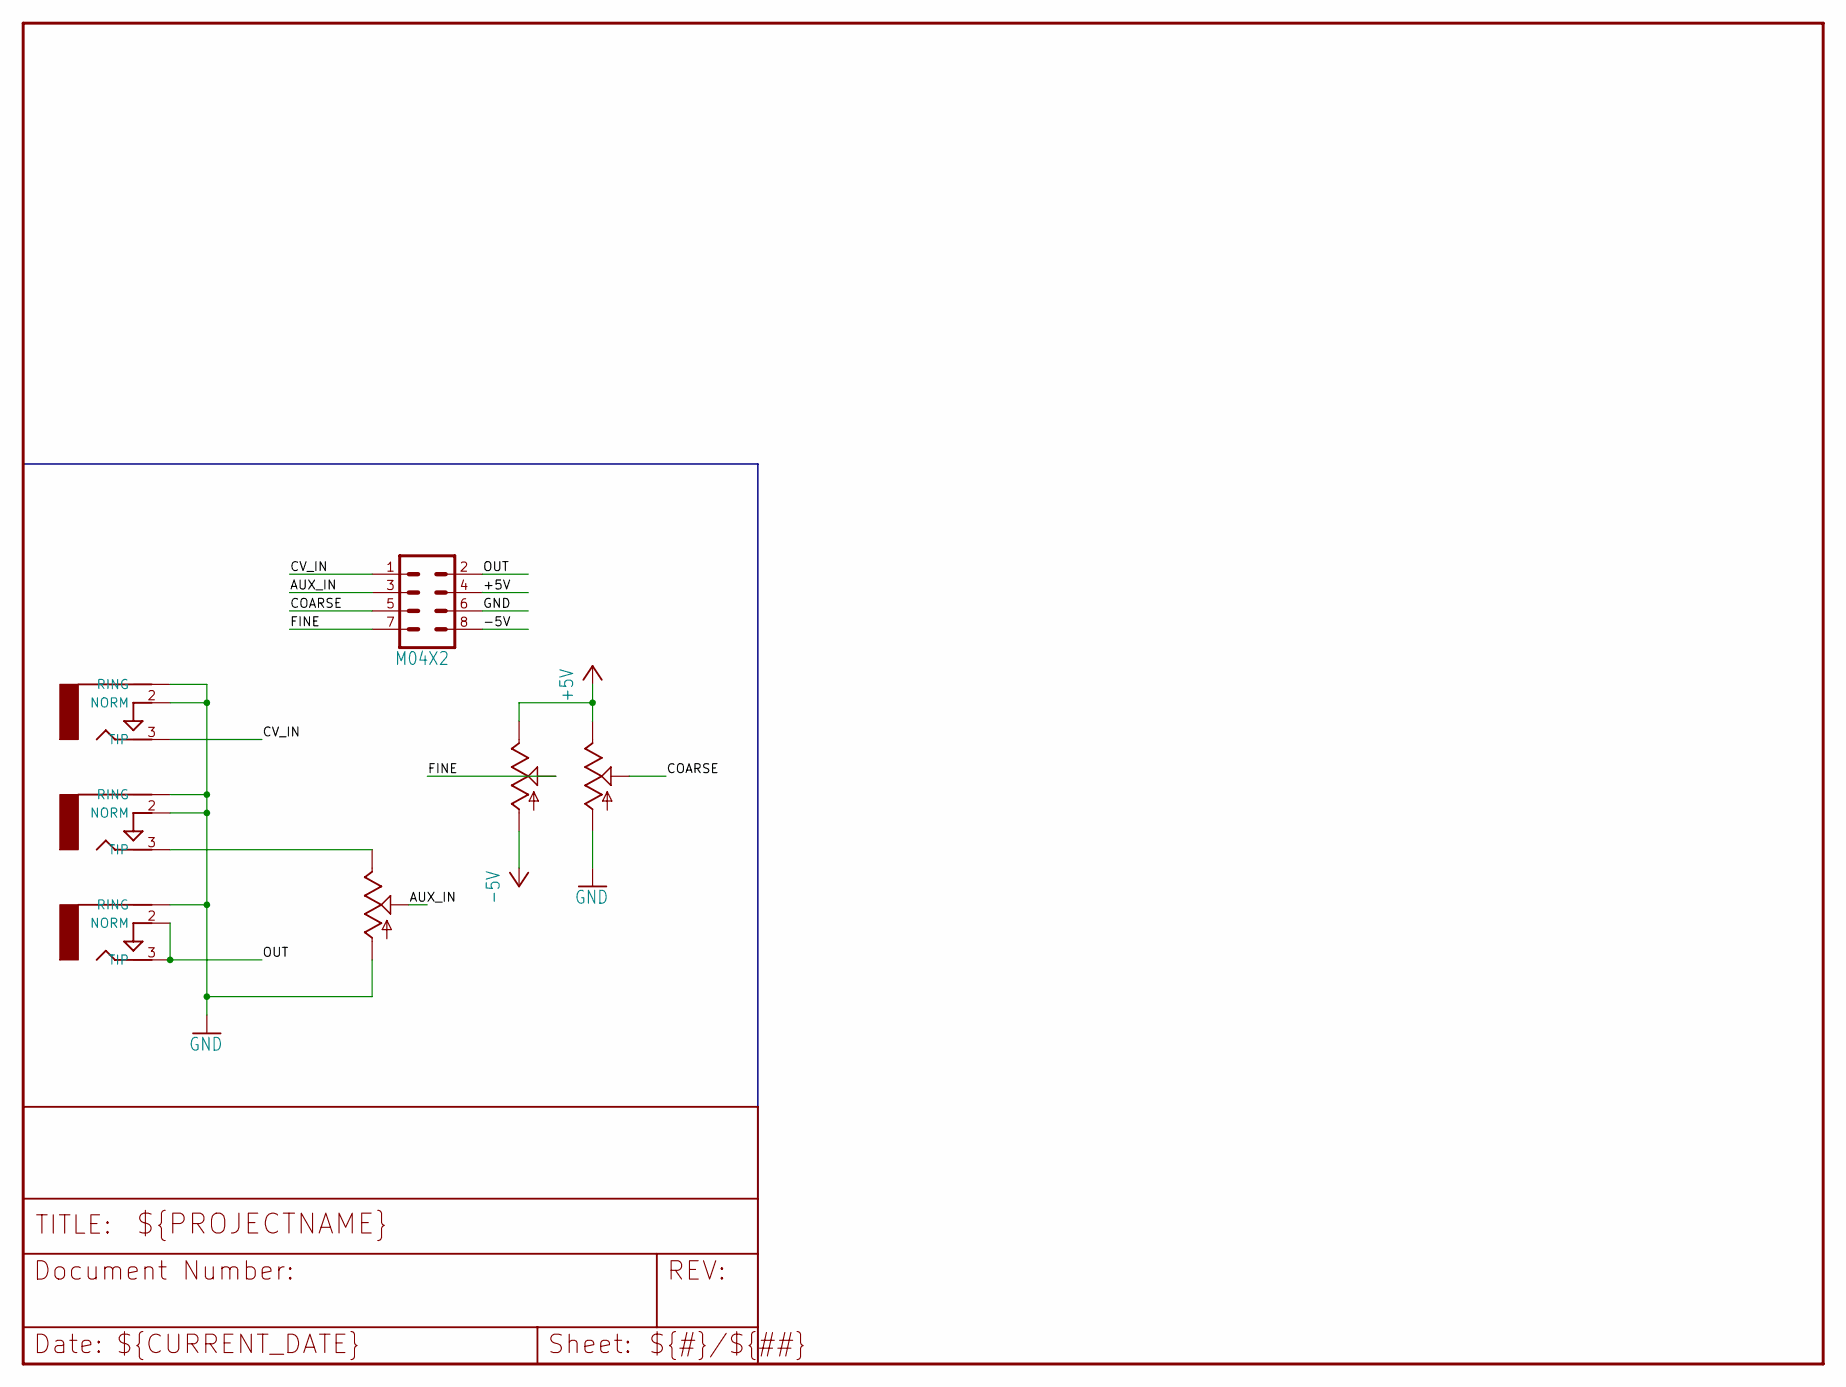
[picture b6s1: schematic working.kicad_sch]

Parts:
AUX_IN0: AUDIO-JACKERTHENVAR; ERTHENVAR-JACK
CV_IN0: AUDIO-JACKERTHENVAR; ERTHENVAR-JACK
OUT0: AUDIO-JACKERTHENVAR; ERTHENVAR-JACK
P1, P2, P3: 100KB; PDB12
PIGGY0: M04X2; 2X4

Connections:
+5V: P2.3 (E), P3.3 (E), PIGGY0.4
-5V: P3.1 (A), PIGGY0.8
AUX_IN: P1.2 (S), PIGGY0.3
COARSE: P2.2 (S), PIGGY0.5
CV_IN: CV_IN0.3 (TIP), PIGGY0.1
FINE: P3.2 (S), PIGGY0.7
GND: AUX_IN0.1@1 (RING), AUX_IN0.1@2 (RING), AUX_IN0.2 (NORM), CV_IN0.1@1 (RING), CV_IN0.1@2 (RING), CV_IN0.2 (NORM), OUT0.1@1 (RING), OUT0.1@2 (RING), P1.1 (A), P2.1 (A), PIGGY0.6
unnamed: AUX_IN0.3 (TIP), P1.3 (E)
OUT: OUT0.2 (NORM), OUT0.3 (TIP), PIGGY0.2

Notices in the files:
projects/rocketman768_chibiamp/version_current/working/working.kicad_pcb:
Licensed under the TAPR Open Hardware License
Copyright 2015, Philip G. Lee
Copyright Philip G. Lee 2015.
projects/russellmcc_basspre_mm2/version_current/working/working.kicad_pcb:
(c) 2014
CC-BY-SA
